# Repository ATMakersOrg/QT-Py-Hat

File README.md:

# QT-Py-Hat
A PCB Board in the shape of a Raspberry Pi HAT that holds a QT Py board as well as the IR circuit from IRLib2

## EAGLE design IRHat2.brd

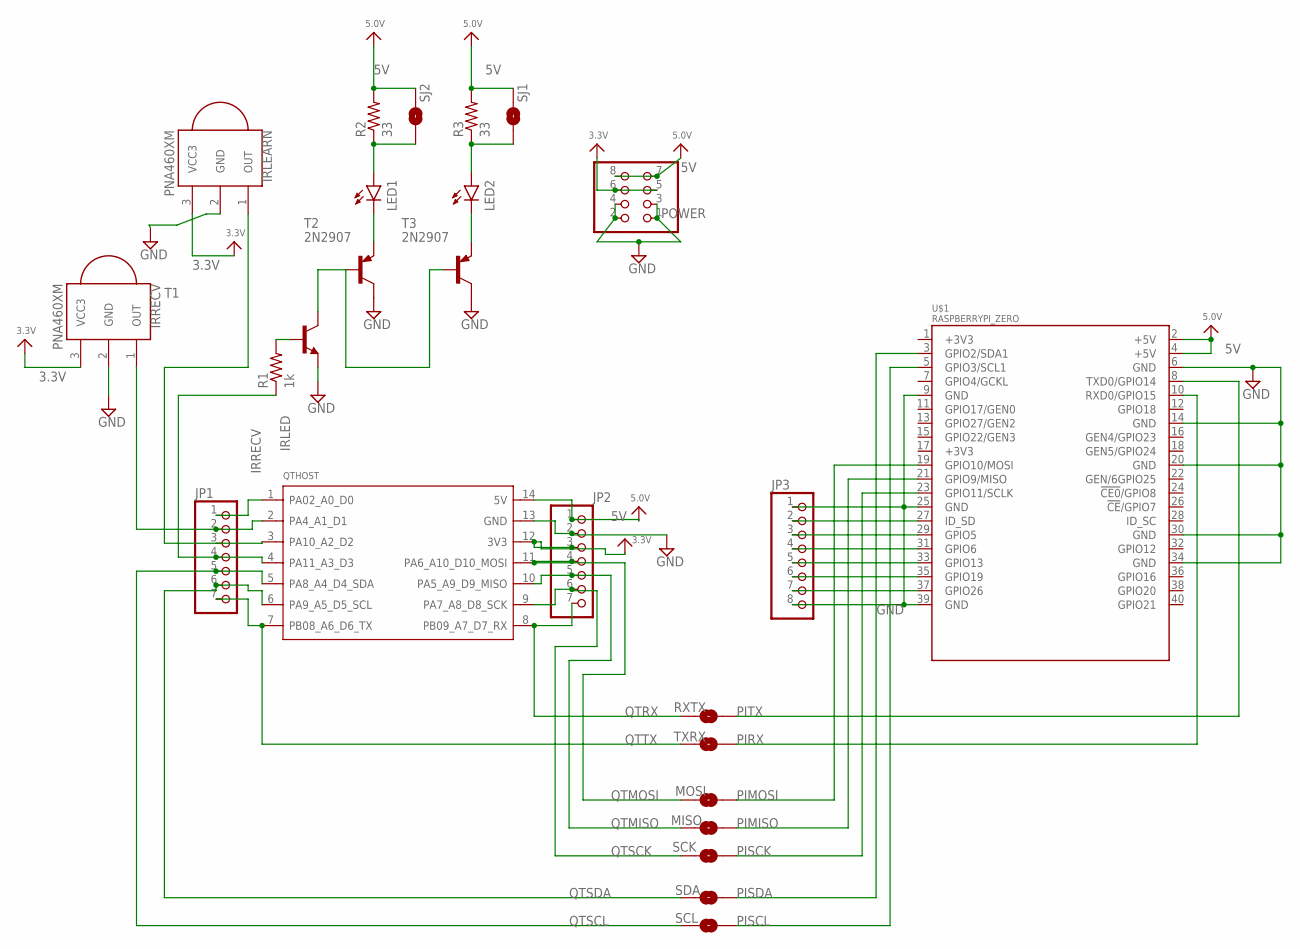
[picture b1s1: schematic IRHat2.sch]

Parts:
IRLEARN: PNA460XM
IRRECV: PNA460XM
JP1, JP2: PINHD-1X7; 1X07
JP3: PINHD-1X8CLEANBIG; 1X08-CLEANBIG
LED1, LED2: LED-IRTSAL6100; LED_5MM
MISO: SPARKFUN_SOLDERJUMPERNO; SPARKFUN_SJ_2S-NO
MOSI: SPARKFUN_SOLDERJUMPERNO; SPARKFUN_SJ_2S-NO
POWER: PINHD-2X4; 2X04
QTHOST: MOUDLE-SEEEDUINO-XIAO; MOUDLE14P-2.54-21X17.8MM
R1: 1k; 0204/5
R2, R3: 33; 0204/5
RXTX: SPARKFUN_SOLDERJUMPERTRACE; SPARKFUN_SJ_2S-TRACE
SCK: SPARKFUN_SOLDERJUMPERNO; SPARKFUN_SJ_2S-NO
SCL: SPARKFUN_SOLDERJUMPERNO; SPARKFUN_SJ_2S-NO
SDA: SPARKFUN_SOLDERJUMPERNO; SPARKFUN_SJ_2S-NO
SJ1, SJ2: SPARKFUN_SOLDERJUMPERTRACE; SPARKFUN_SJ_2S-TRACE
T1: -NPN-TO92-EBC; TO92-EBC
T2, T3: 2N2907; TO92-CBE
TXRX: SPARKFUN_SOLDERJUMPERTRACE; SPARKFUN_SJ_2S-TRACE
U$1: RASPBERRYPI_ZERO

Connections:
3.3V: IRLEARN.3 (VCC3), IRRECV.3 (VCC3), JP2.3, POWER.5, POWER.6, QTHOST.12 (3V3)
5V: JP2.1, POWER.7, POWER.8, QTHOST.14 (5V), R2.2, R3.2, SJ1.2, SJ2.2, U$1.2 (+5V), U$1.4 (+5V)
GND: IRLEARN.2 (GND), IRRECV.2 (GND), JP2.2, JP3.1, JP3.8, POWER.1, POWER.2, POWER.3, POWER.4, QTHOST.13 (GND), T1.E, T2.C, T3.C, U$1.6 (GND), U$1.9 (GND), U$1.14 (GND), U$1.20 (GND), U$1.25 (GND), U$1.30 (GND), U$1.34 (GND), U$1.39 (GND)
IRLED: JP1.4, QTHOST.4 (PA11_A3_D3), R1.1
IRRECV: IRRECV.1 (OUT), JP1.2, QTHOST.2 (PA4_A1_D1)
unnamed: JP3.2, U$1.27 (ID_SD)
unnamed: JP3.3, U$1.29 (GPIO5)
unnamed: LED1.K (C), T2.E
unnamed: R1.2, T1.B
unnamed: LED2.K (C), T3.E
unnamed: JP3.4, U$1.31 (GPIO6)
unnamed: LED2.A, R3.1, SJ1.1
unnamed: T1.C, T2.B, T3.B
unnamed: JP1.1, QTHOST.1 (PA02_A0_D0)
unnamed: LED1.A, R2.1, SJ2.1
unnamed: JP3.5, U$1.33 (GPIO13)
unnamed: IRLEARN.1 (OUT), JP1.3, QTHOST.3 (PA10_A2_D2)
unnamed: JP3.6, U$1.35 (GPIO19)
unnamed: JP3.7, U$1.37 (GPIO26)
PIMISO: MISO.2, U$1.21 (GPIO9/MISO)
PIMOSI: MOSI.2, U$1.19 (GPIO10/MOSI)
PIRX: TXRX.2, U$1.10 (RXD0/GPIO15)
PISCK: SCK.2, U$1.23 (GPIO11/SCLK)
PISCL: SCL.2, U$1.5 (GPIO3/SCL1)
PISDA: SDA.2, U$1.3 (GPIO2/SDA1)
PITX: RXTX.2, U$1.8 (TXD0/GPIO14)
QTMISO: JP2.5, MISO.1, QTHOST.10 (PA5_A9_D9_MISO)
QTMOSI: JP2.4, MOSI.1, QTHOST.11 (PA6_A10_D10_MOSI)
QTRX: JP2.7, QTHOST.8 (PB09_A7_D7_RX), RXTX.1
QTSCK: JP2.6, QTHOST.9 (PA7_A8_D8_SCK), SCK.1
QTSCL: JP1.5, QTHOST.5 (PA8_A4_D4_SDA), SCL.1
QTSDA: JP1.6, QTHOST.6 (PA9_A5_D5_SCL), SDA.1
QTTX: JP1.7, QTHOST.7 (PB08_A6_D6_TX), TXRX.1

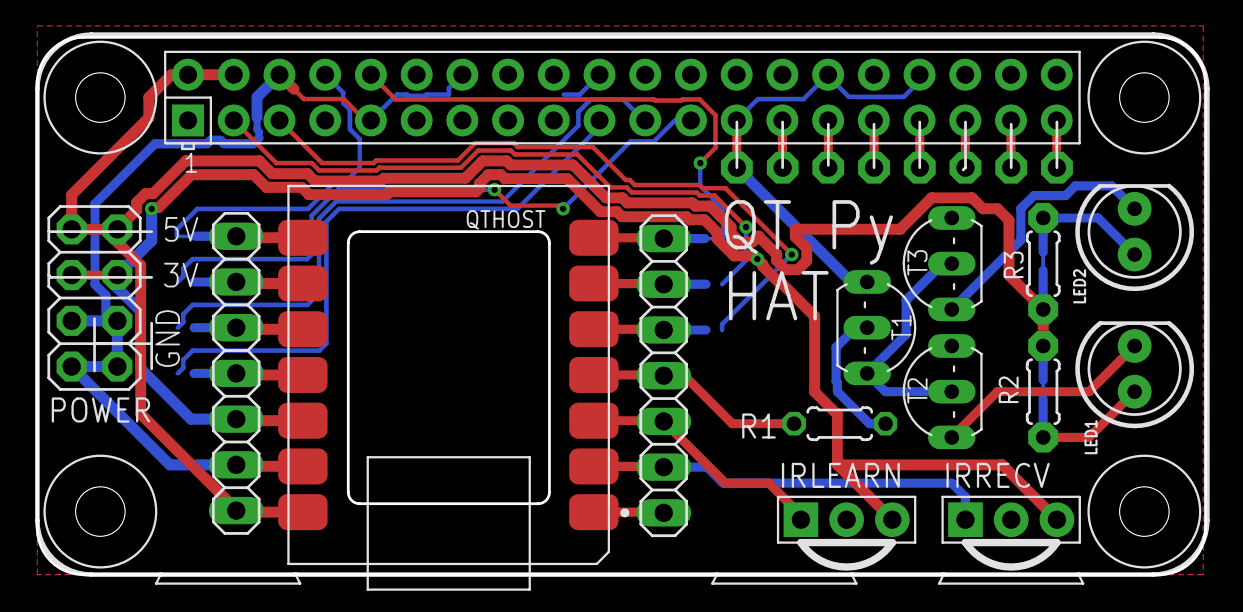
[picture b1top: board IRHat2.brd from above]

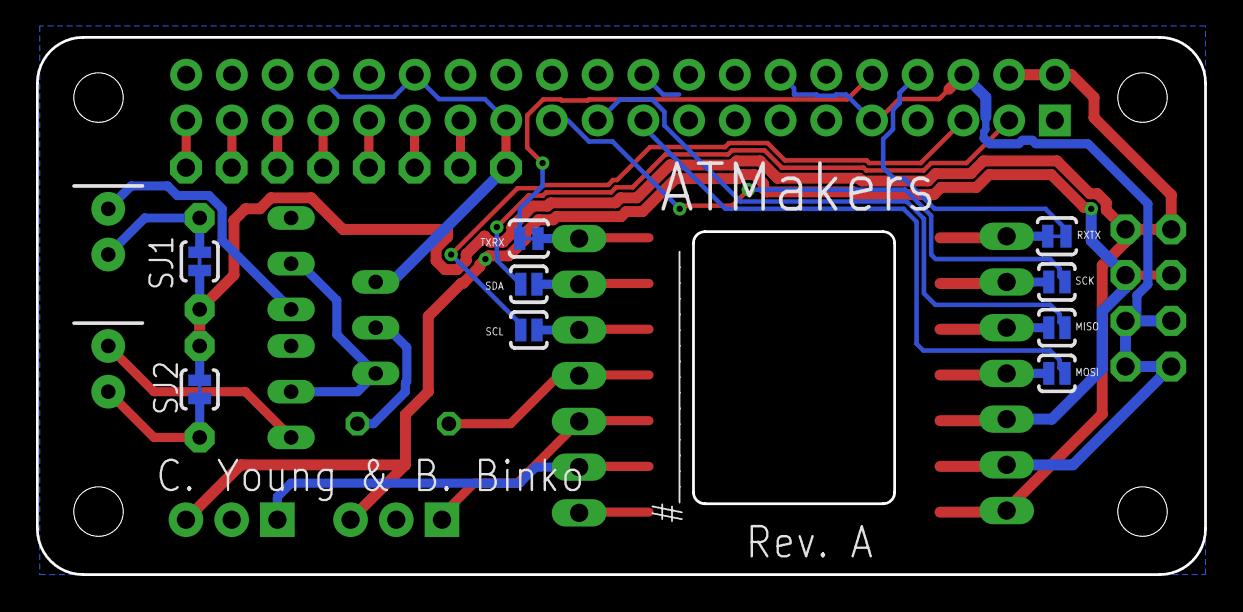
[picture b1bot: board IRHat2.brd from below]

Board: 2 copper layers, 64.9 x 29.8 mm, 25 parts (9 on the bottom side), 33 nets.

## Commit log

2021-02-07 Initial Upload
    This is the first drop after Chris and Bill discussed the board
2021-02-07 tweaks and warning fixes

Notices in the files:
parts and their libraries:
SparkFun-LED: Licensing: Creative Commons ShareAlike 4.0 International - https://creativecommons.org/licenses/by-sa/4.0
microbuilder: This work is placed in the public domain, and may be freely used for commercial and non-commercial work with the following conditions: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
